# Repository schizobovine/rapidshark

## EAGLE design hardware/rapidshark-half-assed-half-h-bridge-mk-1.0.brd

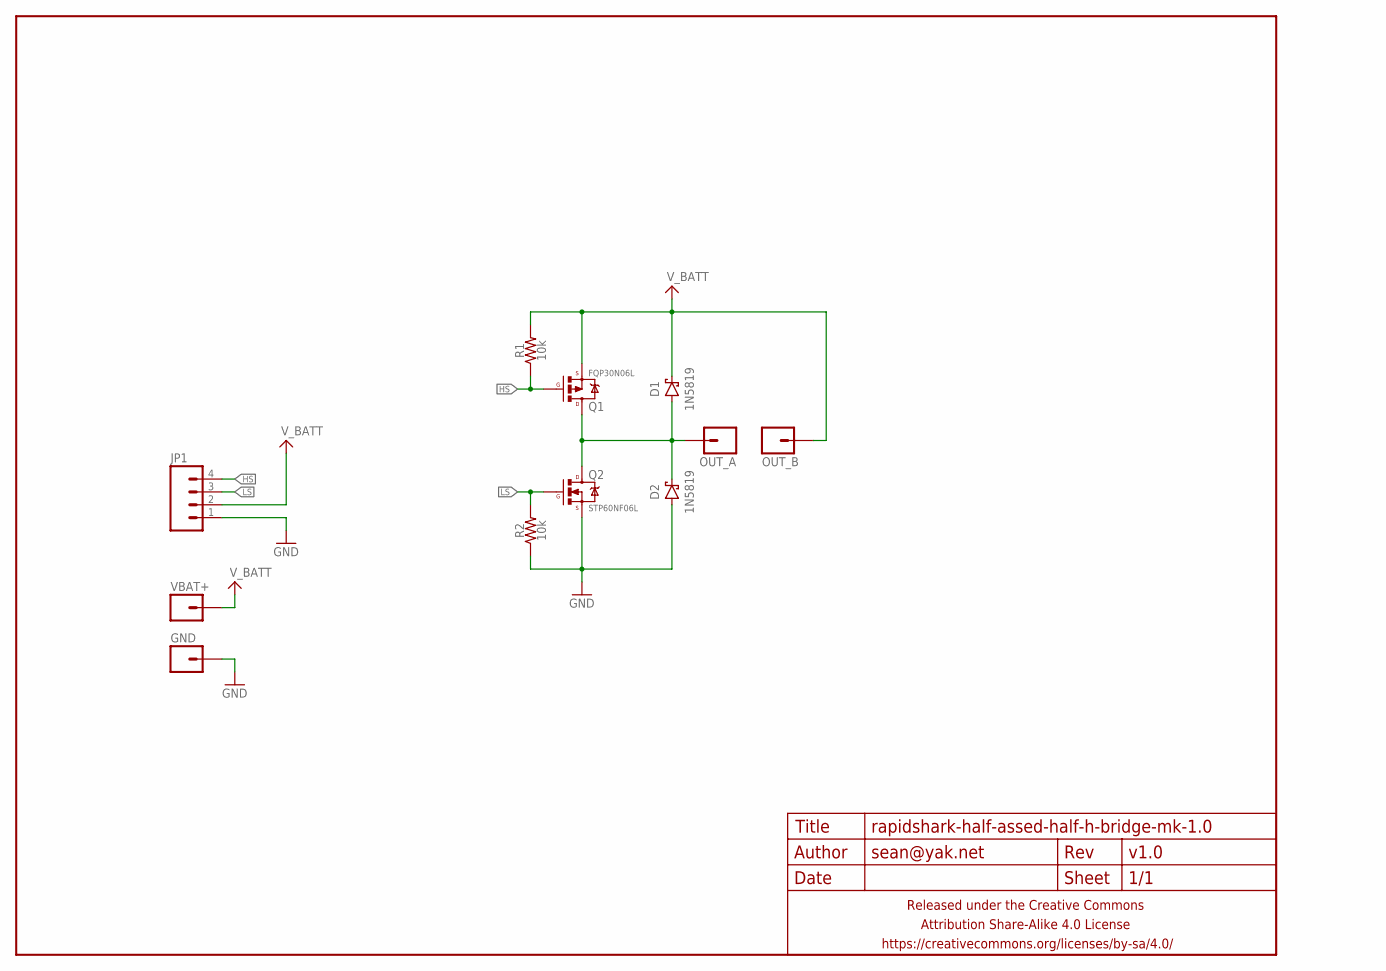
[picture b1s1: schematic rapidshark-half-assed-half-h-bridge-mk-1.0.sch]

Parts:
D1, D2: 1N5819; DIODE-SCHOTTKY-10.16MM
FRAME1: FRAME-LETTERNO_PACKAGE; DUMMY
GND: M0112AWG; 1X01-12AWG
JP1: M04PTH; 1X04-PTH-VERT
OUT_A: M0112AWG; 1X01-12AWG
OUT_B: M0112AWG; 1X01-12AWG
Q1: FQP30N06L; TO220-THERMPAD
Q2: STP60NF06L; TO220-THERMPAD
R1, R2: 10k; RESISTOR-AXIAL-PTH-5.08MM
VBAT+: M0112AWG; 1X01-12AWG

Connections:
A: D1.A, D2.C, OUT_A.1, Q1.2@1 (D), Q1.2@2 (D), Q2.2@1 (D), Q2.2@2 (D)
GND: D2.A, GND.1, JP1.1, Q2.3 (S), R2.P$1 (1)
HS: JP1.4, Q1.1 (G), R1.P$1 (1)
LS: JP1.3, Q2.1 (G), R2.P$2 (2)
V_BATT: D1.C, JP1.2, OUT_B.1, Q1.3 (S), R1.P$2 (2), VBAT+.1

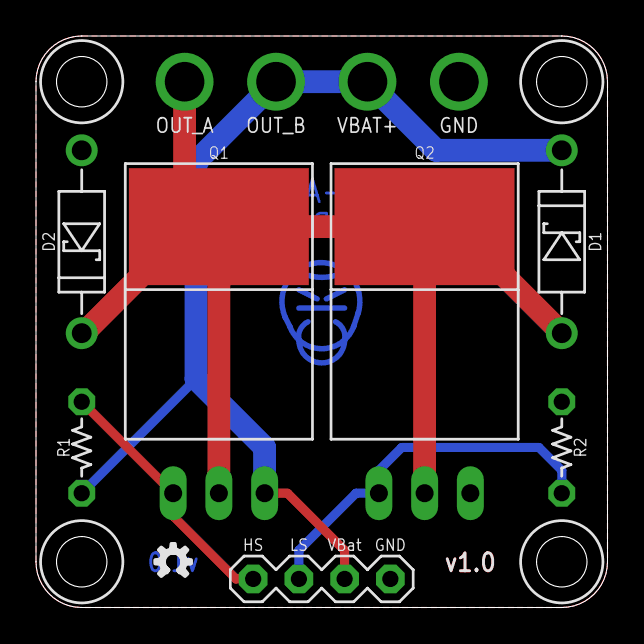
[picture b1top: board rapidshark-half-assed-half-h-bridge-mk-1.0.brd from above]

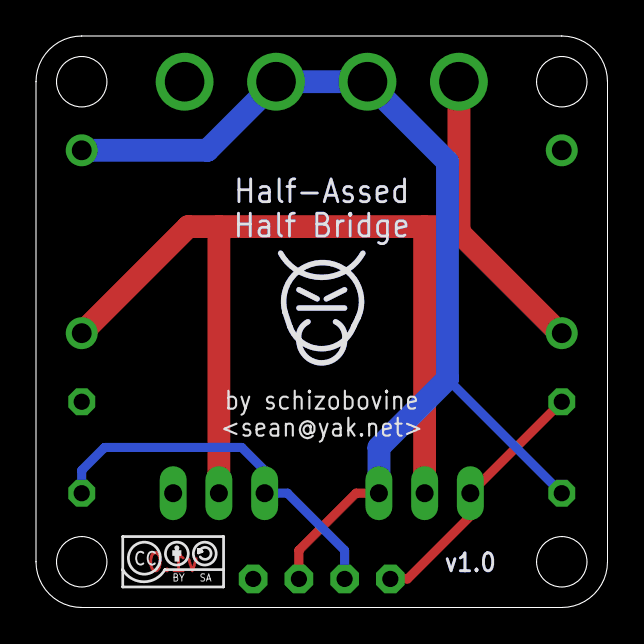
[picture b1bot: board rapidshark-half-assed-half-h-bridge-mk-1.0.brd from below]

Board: 2 copper layers, 31.8 x 31.8 mm, 15 parts (3 on the bottom side), 5 nets.

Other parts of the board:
U$1: COW_SMALL_METAL_NOTEXT
U$2: CC-BY-SA-4.0-NO-URL
U$3: OSHWLOGO_TINY_SILKONLY

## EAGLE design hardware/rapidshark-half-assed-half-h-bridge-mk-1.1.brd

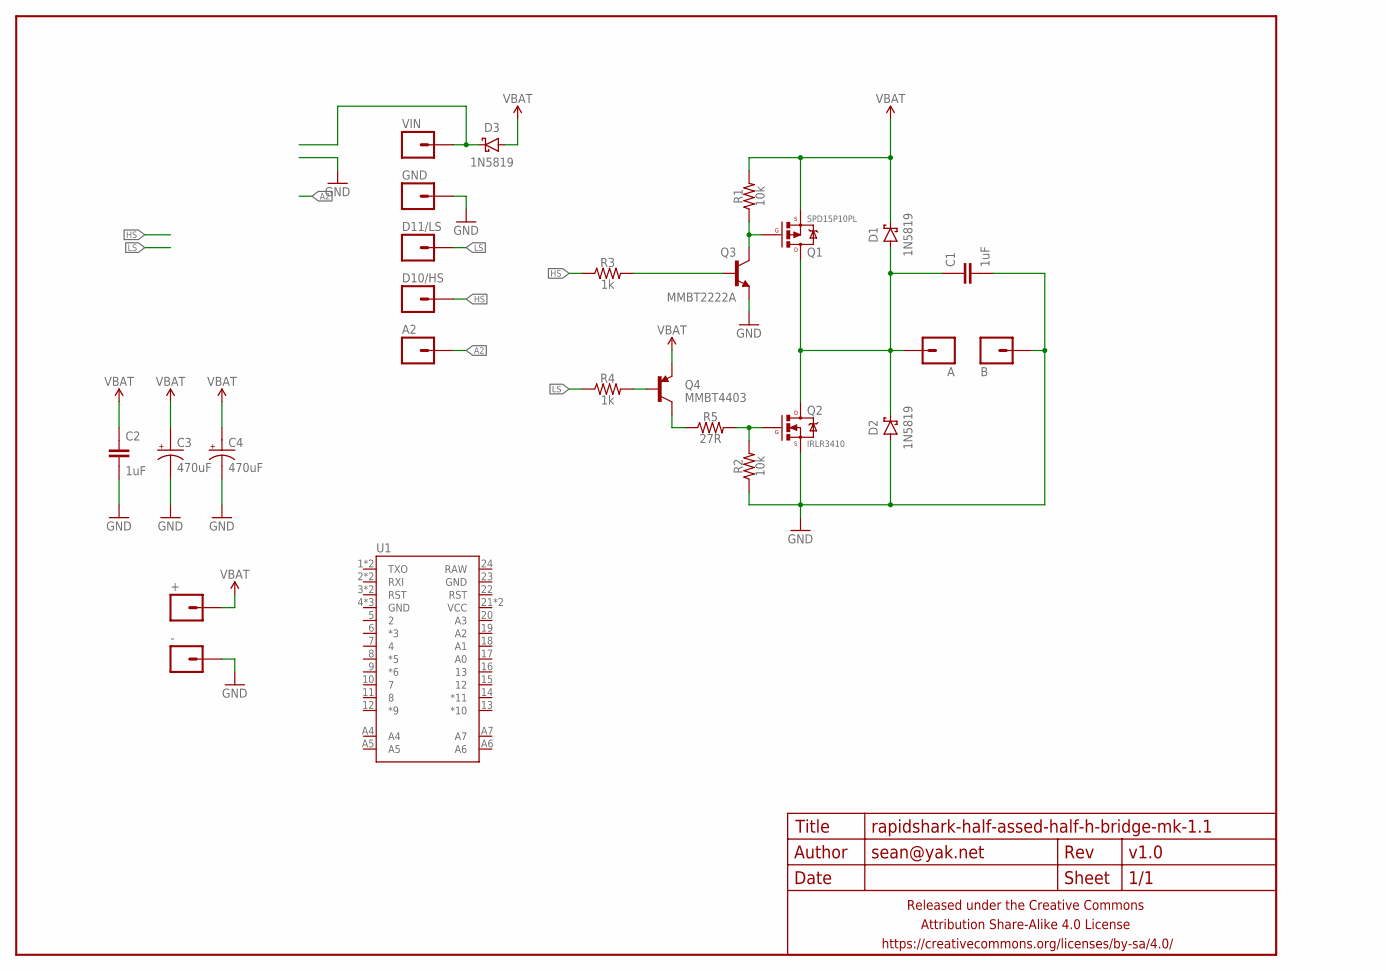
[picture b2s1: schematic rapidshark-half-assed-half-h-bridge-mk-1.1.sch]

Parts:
+: M01PTH-1.4MM; 1X01-1.4MM-CIR
-: M01PTH-1.4MM; 1X01-1.4MM-CIR
A: M01PTH-1.4MM; 1X01-1.4MM-CIR
A2: M01PTH; 1X01
B: M01PTH-1.4MM; 1X01-1.4MM-CIR
C1, C2: 1uF; C0603-TIGHTER
C3, C4: 470uF; E5-10,5
D1, D2: 1N5819; SMA-DIODE-SCHOTTKY
D3: 1N5819; SOD323-SCHOTTKY
D10/HS, D11/LS: M01PTH; 1X01
FRAME1: FRAME-LETTERNO_PACKAGE; DUMMY
GND: M01PTH; 1X01
Q1: SPD15P10PL; DPAK
Q2: IRLR3410; DPAK
Q3: MMBT2222A; SOT23
Q4: MMBT4403; SOT23
R1, R2: 10k; R0603-TIGHTER
R3, R4: 1k; R0603-TIGHTER
R5: 27R; R0603-TIGHTER
U1: ARDUINO_PRO_MINIMINE; ARDUINO_PRO_MINI_MINE
VIN: M01PTH; 1X01

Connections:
A: A.P$1, C1.1, D1.A, D2.C, Q1.4 (D), Q2.4 (D)
GND: -.P$1, B.P$1, C1.2, C2.2, C3.-, C4.-, D2.A, GND.1, Q2.3 (S), Q3.2 (E), R2.1
HS: D10/HS.1, R3.1
LS: D11/LS.1, R4.1
unnamed: Q1.1 (G), Q3.3 (C), R1.1
unnamed: Q2.1 (G), R2.2, R5.2
unnamed: Q3.1 (B), R3.2
unnamed: Q4.1 (B), R4.2
unnamed: Q4.3 (C), R5.1
unnamed: D3.C, VIN.1
VBAT: +.P$1, C2.1, C3.+, C4.+, D1.C, D3.A, Q1.3 (S), Q4.2 (E), R1.2

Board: 2 copper layers, 30 parts (23 on the bottom side), 11 nets, no tracks yet.

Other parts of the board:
U$1: COW_SMALL_METAL_NOTEXT
U$2: CC-BY-SA-4.0-NO-URL
U$3: OSHWLOGO_TINY_SILKONLY

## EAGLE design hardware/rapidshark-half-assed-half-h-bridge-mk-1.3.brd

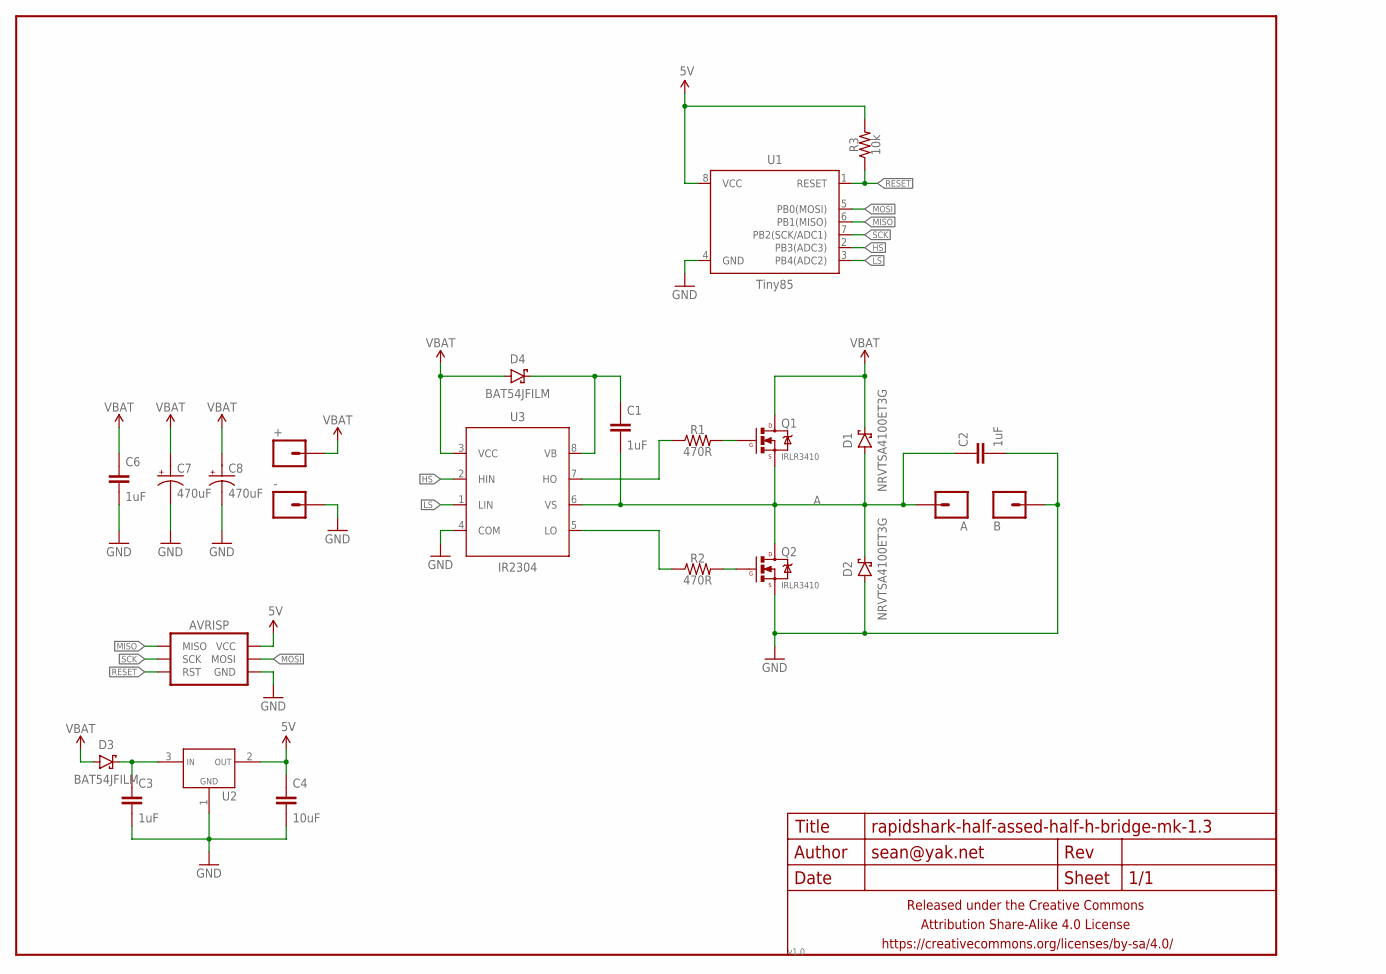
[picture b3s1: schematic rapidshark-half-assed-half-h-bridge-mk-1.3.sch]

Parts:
+: M01PTH-1.4MM; 1X01-1.4MM-CIR
-: M01PTH-1.4MM; 1X01-1.4MM-CIR
A: M01PTH-1.4MM; 1X01-1.4MM-CIR
AVRISP: AVR_SPI_PRG_6INLINE; AVR_MINI_PROG
B: M01PTH-1.4MM; 1X01-1.4MM-CIR
C1, C2, C3, C6: 1uF; C0603-TIGHTER
C4: 10uF; C0805-TIGHTER
C7, C8: 470uF; E5-10,5
D1, D2: NRVTSA4100ET3G; SMA-DIODE-SCHOTTKY
D3, D4: BAT54JFILM; SOD323-SCHOTTKY
FRAME1: FRAME-LETTERNO_PACKAGE; DUMMY
Q1, Q2: IRLR3410; DPAK
R1, R2: 470R; R0603-TIGHTER
R3: 10k; R0603-TIGHTER
U1: Tiny85; SO08-EIAJ
U2: VREG_1117SOT-23; SOT23
U3: IR2304; SO08

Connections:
5V: AVRISP.2 (VCC), C4.1, R3.2, U1.8 (VCC), U2.2 (VOUT)
A: A.P$1, C1.2, C2.1, D1.A, D2.C, Q1.3 (S), Q2.4 (D), U3.6 (VS)
GND: -.P$1, AVRISP.6 (GND), B.P$1, C2.2, C3.2, C4.2, C6.2, C7.-, C8.-, D2.A, Q2.3 (S), U1.4 (GND), U2.1 (GND), U3.4 (COM)
HS: U1.2 (PB3(ADC3)), U3.2 (HIN)
LS: U1.3 (PB4(ADC2)), U3.1 (LIN)
MISO: AVRISP.1 (MISO), U1.6 (PB1(MISO))
MOSI: AVRISP.4 (MOSI), U1.5 (PB0(MOSI))
unnamed: Q1.1 (G), R1.2
unnamed: Q2.1 (G), R2.2
unnamed: R1.1, U3.7 (HO)
unnamed: R2.1, U3.5 (LO)
unnamed: C1.1, D4.C, U3.8 (VB)
unnamed: C3.1, D3.C, U2.3 (VIN)
RESET: AVRISP.5 (RST), R3.1, U1.1 (RESET)
SCK: AVRISP.3 (SCK), U1.7 (PB2(SCK/ADC1))
VBAT: +.P$1, C6.1, C7.+, C8.+, D1.C, D3.A, D4.A, Q1.4 (D), U3.3 (VCC)

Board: 2 copper layers, 28 parts (4 on the bottom side), 16 nets, no tracks yet.

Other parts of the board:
U$1: COW_SMALL_METAL_NOTEXT
U$2: CC-BY-SA-4.0-NO-URL
U$3: OSHWLOGO_TINY_SILKONLY

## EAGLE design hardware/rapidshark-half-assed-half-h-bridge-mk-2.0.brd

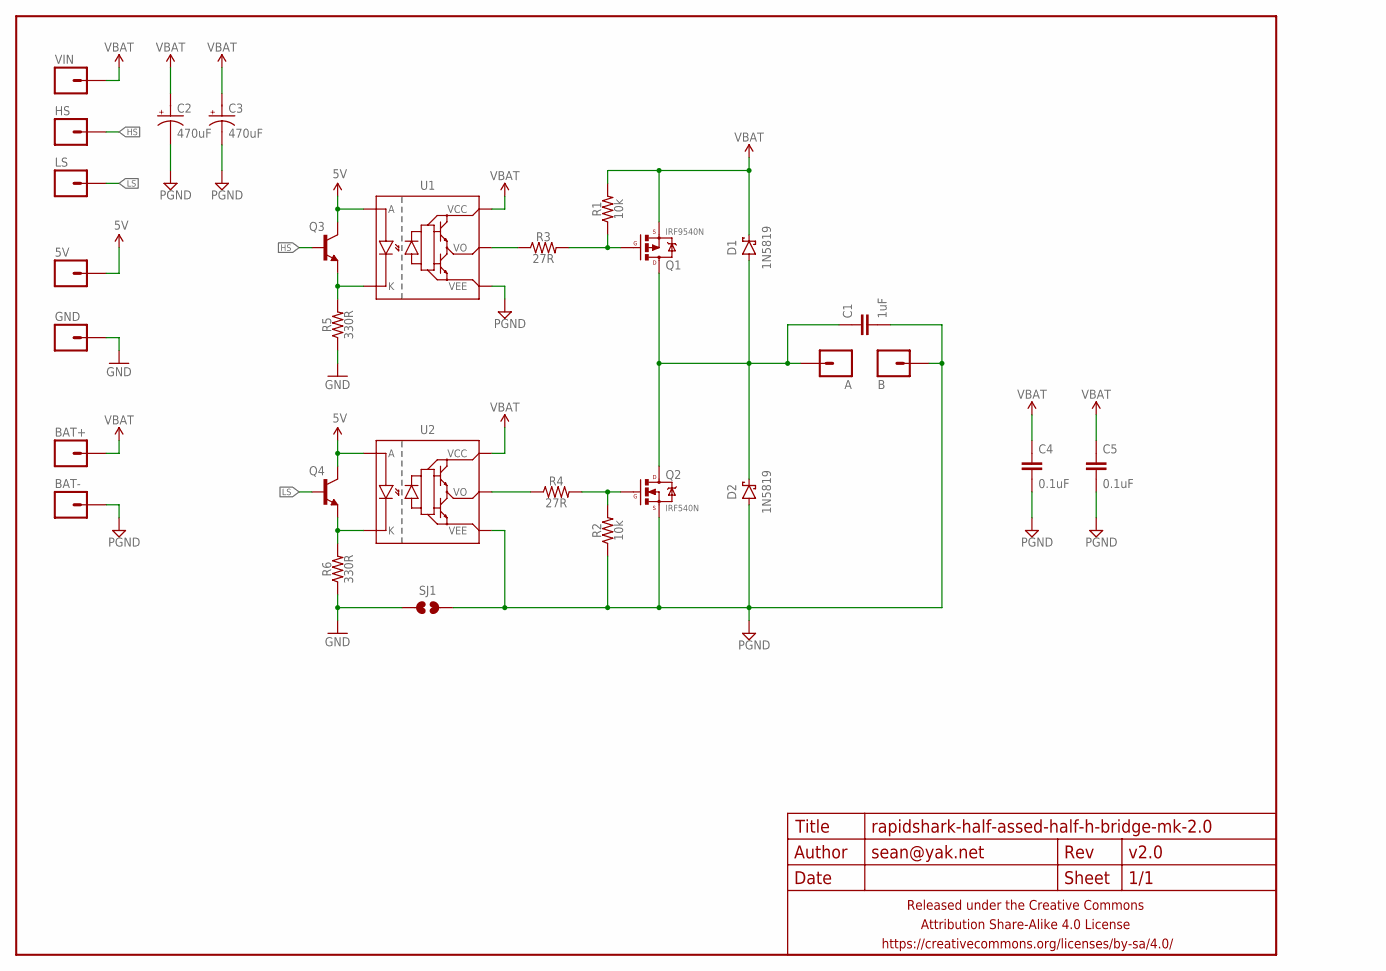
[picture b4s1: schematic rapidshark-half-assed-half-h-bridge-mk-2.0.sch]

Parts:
5V: M01PTH; 1X01
A: M01PTH-1.9MM; 1X01-1.9MM-CIR
B: M01PTH-1.9MM; 1X01-1.9MM-CIR
BAT+: M01PTH-1.9MM; 1X01-1.9MM-CIR
BAT-: M01PTH-1.9MM; 1X01-1.9MM-CIR
C1: 1uF; C0603-TIGHTER
C2, C3: 470uF; E5-10,5
C4, C5: 0.1uF; C0603-TIGHTER
D1, D2: 1N5819; SMA-DIODE-SCHOTTKY
FRAME1: FRAME-LETTERNO_PACKAGE; DUMMY
GND: M01PTH; 1X01
HS: M01PTH; 1X01
LS: M01PTH; 1X01
Q1: IRF9540N; D2PAK
Q2: IRF540N; D2PAK
Q3, Q4: TRANSISTOR_NPNMMBT2222A; SOT23
R1, R2: 10k; R0603-TIGHTER
R3, R4: 27R; R0603-TIGHTER
R5, R6: 330R; R0603-TIGHTER
SJ1: JUMPER-PAD-2-NO; PAD-JUMPER-2-NO_NO_SILK
U1, U2: OPTOISOLATOR-GATEDRIVERSOIC05; SO05
VIN: M01PTH; 1X01

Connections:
5V: 5V.1, Q3.3 (C), Q4.3 (C), U1.1 (A), U2.1 (A)
A: A.P$1, C1.1, D1.A, D2.C, Q1.D, Q2.D
GND: GND.1, R5.1, R6.1, SJ1.1
HS: HS.1, Q3.1 (B)
LS: LS.1, Q4.1 (B)
unnamed: Q2.G, R2.2, R4.2
unnamed: R3.1, U1.5 (VO)
unnamed: Q3.2 (E), R5.2, U1.3 (K)
unnamed: Q1.G, R1.1, R3.2
unnamed: Q4.2 (E), R6.2, U2.3 (K)
unnamed: R4.1, U2.5 (VO)
PGND: B.P$1, BAT-.P$1, C1.2, C2.-, C3.-, C4.2, C5.2, D2.A, Q2.S, R2.1, SJ1.2, U1.4 (VEE), U2.4 (VEE)
VBAT: BAT+.P$1, C2.+, C3.+, C4.1, C5.1, D1.C, Q1.S, R1.2, U1.6 (VCC), U2.6 (VCC), VIN.1

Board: 2 copper layers, 30 parts (2 on the bottom side), 13 nets, no tracks yet.

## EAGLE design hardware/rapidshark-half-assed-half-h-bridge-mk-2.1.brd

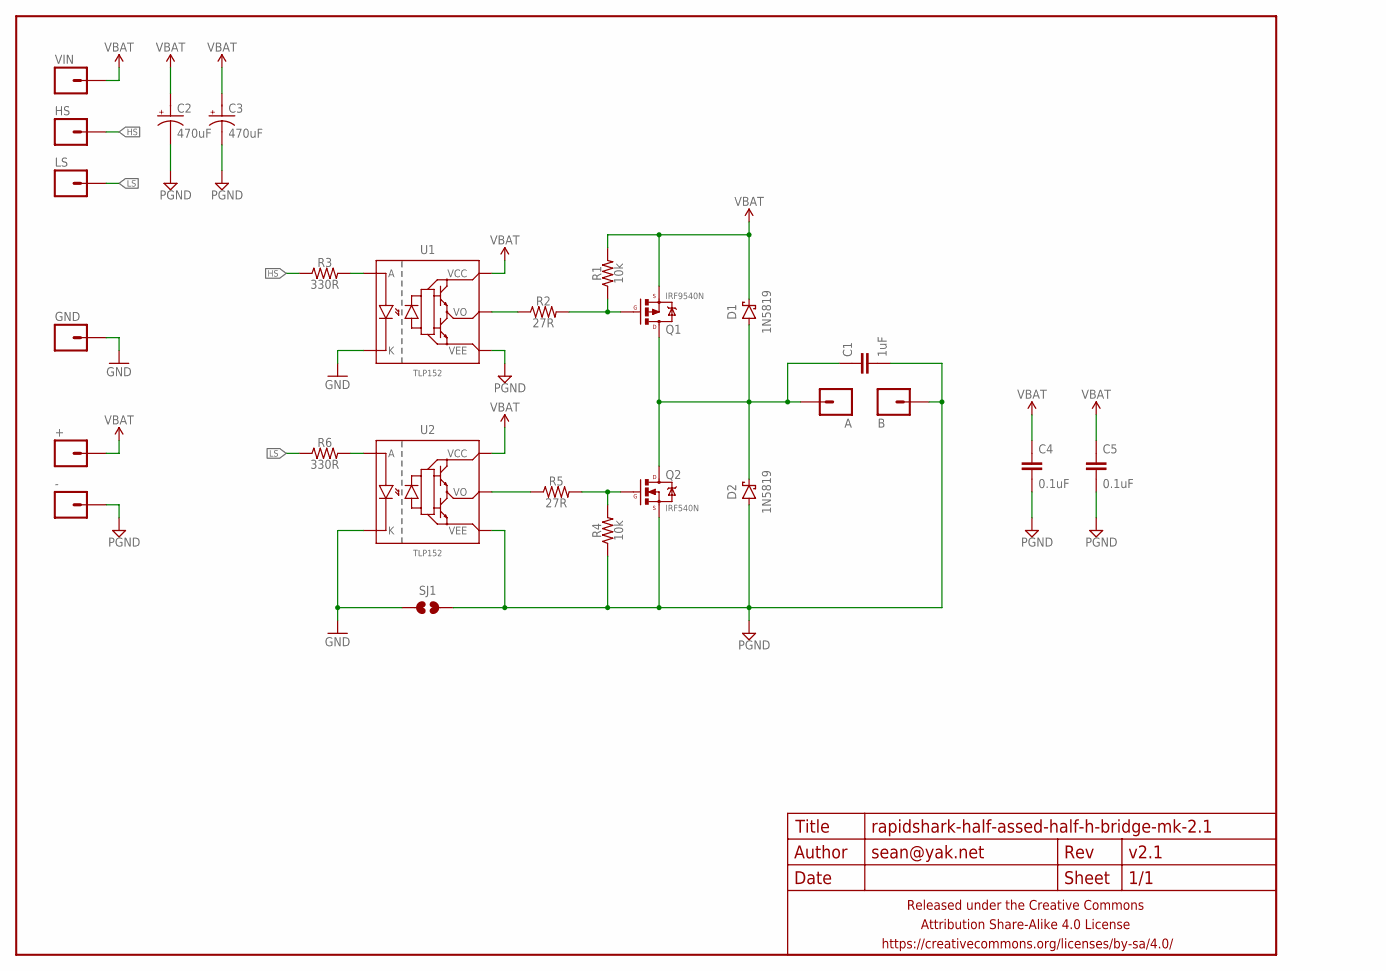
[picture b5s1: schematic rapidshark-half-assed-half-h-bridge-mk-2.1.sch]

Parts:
+: M01PTH-1.9MM; 1X01-1.9MM-CIR
-: M01PTH-1.9MM; 1X01-1.9MM-CIR
A: M01PTH-1.9MM; 1X01-1.9MM-CIR
B: M01PTH-1.9MM; 1X01-1.9MM-CIR
C1: 1uF; C0603-TIGHTER
C2, C3: 470uF; E5-10,5
C4, C5: 0.1uF; C0603-TIGHTER
D1, D2: 1N5819; SMA-DIODE-SCHOTTKY
FRAME1: FRAME-LETTERNO_PACKAGE; DUMMY
GND: M01PTH; 1X01
HS: M01PTH; 1X01
LS: M01PTH; 1X01
Q1: IRF9540N; D2PAK
Q2: IRF540N; D2PAK
R1, R4: 10k; R0603-TIGHTER
R2, R5: 27R; R0603-TIGHTER
R3, R6: 330R; R0603-TIGHTER
SJ1: JUMPER-PAD-2-NO; PAD-JUMPER-2-NO_NO_SILK
U1, U2: TLP152; SO05
VIN: M01PTH; 1X01

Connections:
A: A.P$1, C1.1, D1.A, D2.C, Q1.D, Q2.D
GND: GND.1, SJ1.1, U1.3 (K), U2.3 (K)
HS: HS.1, R3.1
LS: LS.1, R6.1
unnamed: Q2.G, R4.2, R5.2
unnamed: R2.1, U1.5 (VO)
unnamed: R6.2, U2.1 (A)
unnamed: R3.2, U1.1 (A)
unnamed: Q1.G, R1.1, R2.2
unnamed: R5.1, U2.5 (VO)
PGND: -.P$1, B.P$1, C1.2, C2.-, C3.-, C4.2, C5.2, D2.A, Q2.S, R4.1, SJ1.2, U1.4 (VEE), U2.4 (VEE)
VBAT: +.P$1, C2.+, C3.+, C4.1, C5.1, D1.C, Q1.S, R1.2, U1.6 (VCC), U2.6 (VCC), VIN.1

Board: 2 copper layers, 27 parts (2 on the bottom side), 12 nets, no tracks yet.

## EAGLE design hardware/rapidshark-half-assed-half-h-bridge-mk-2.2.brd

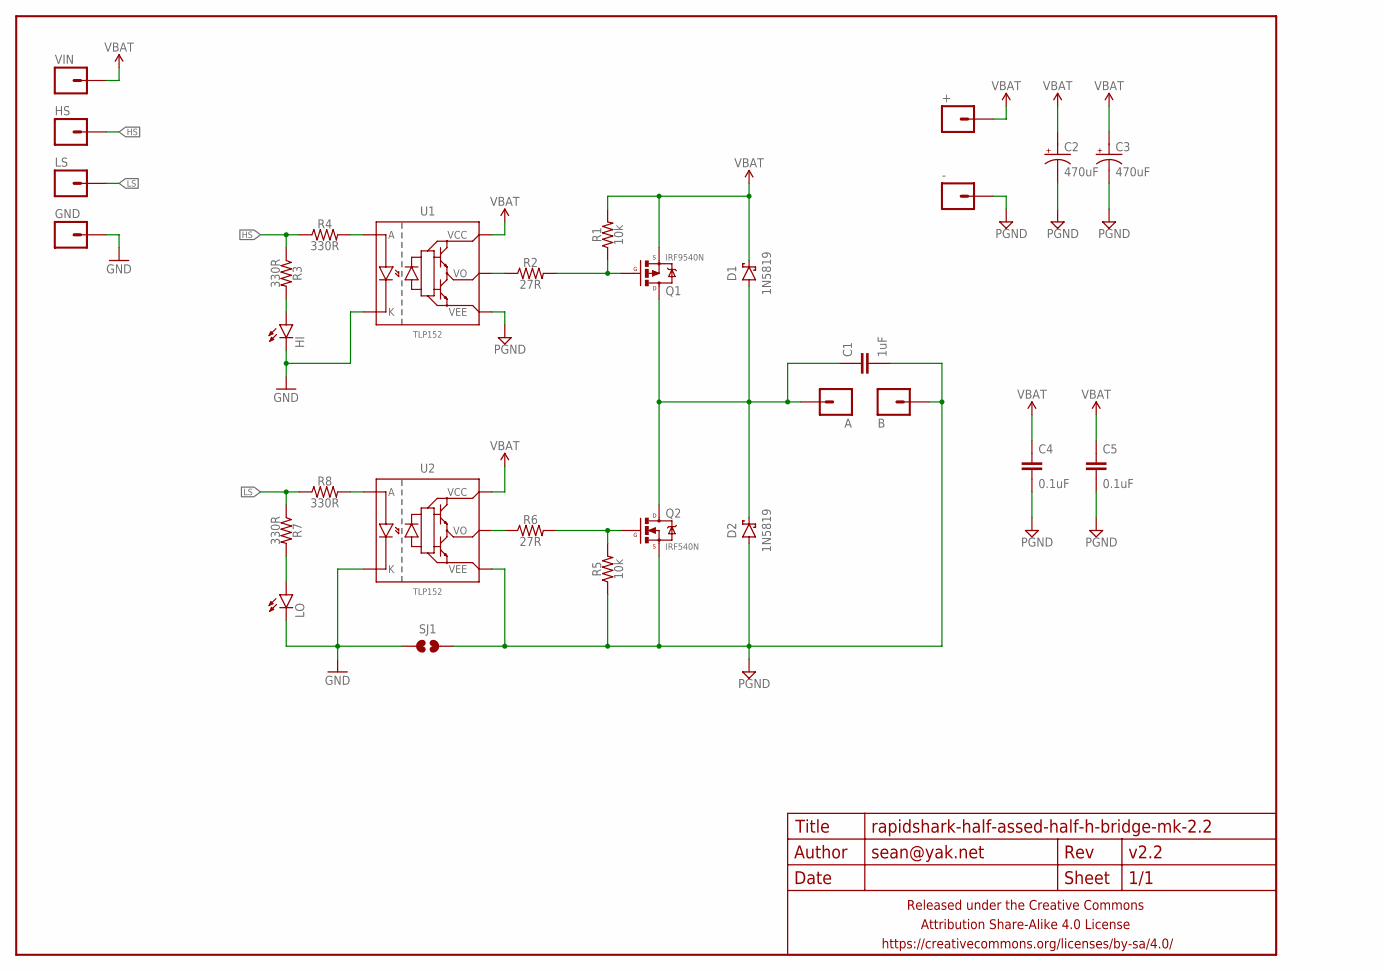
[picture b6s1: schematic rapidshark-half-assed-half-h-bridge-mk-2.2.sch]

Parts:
+: M01PTH-1.9MM; 1X01-1.9MM-CIR
-: M01PTH-1.9MM; 1X01-1.9MM-CIR
A: M01PTH-1.9MM; 1X01-1.9MM-CIR
B: M01PTH-1.9MM; 1X01-1.9MM-CIR
C1: 1uF; C0603-TIGHTER
C2, C3: 470uF; E5-10,5
C4, C5: 0.1uF; C0603-TIGHTER
D1, D2: 1N5819; SMA-DIODE-SCHOTTKY
FRAME1: FRAME-LETTERNO_PACKAGE; DUMMY
GND: M01PTH; 1X01
HI: LED0603-TIGHT; LED-0603-TIGHT
HS: M01PTH; 1X01
LO: LED0603-TIGHT; LED-0603-TIGHT
LS: M01PTH; 1X01
Q1: IRF9540N; D2PAK
Q2: IRF540N; D2PAK
R1, R5: 10k; R0603-TIGHTER
R2, R6: 27R; R0603-TIGHTER
R3, R4, R7, R8: 330R; R0603-TIGHTER
SJ1: JUMPER-PAD-2-NO; PAD-JUMPER-2-NO_NO_SILK
U1, U2: TLP152; SO05
VIN: M01PTH; 1X01

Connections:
A: A.P$1, C1.1, D1.A, D2.C, Q1.D, Q2.D
GND: GND.1, HI.C, LO.C, SJ1.1, U1.3 (K), U2.3 (K)
HS: HS.1, R3.1, R4.1
LS: LS.1, R7.1, R8.1
unnamed: Q2.G, R5.2, R6.2
unnamed: R2.1, U1.5 (VO)
unnamed: LO.A, R7.2
unnamed: HI.A, R3.2
unnamed: Q1.G, R1.1, R2.2
unnamed: R4.2, U1.1 (A)
unnamed: R8.2, U2.1 (A)
unnamed: R6.1, U2.5 (VO)
PGND: -.P$1, B.P$1, C1.2, C2.-, C3.-, C4.2, C5.2, D2.A, Q2.S, R5.1, SJ1.2, U1.4 (VEE), U2.4 (VEE)
VBAT: +.P$1, C2.+, C3.+, C4.1, C5.1, D1.C, Q1.S, R1.2, U1.6 (VCC), U2.6 (VCC), VIN.1

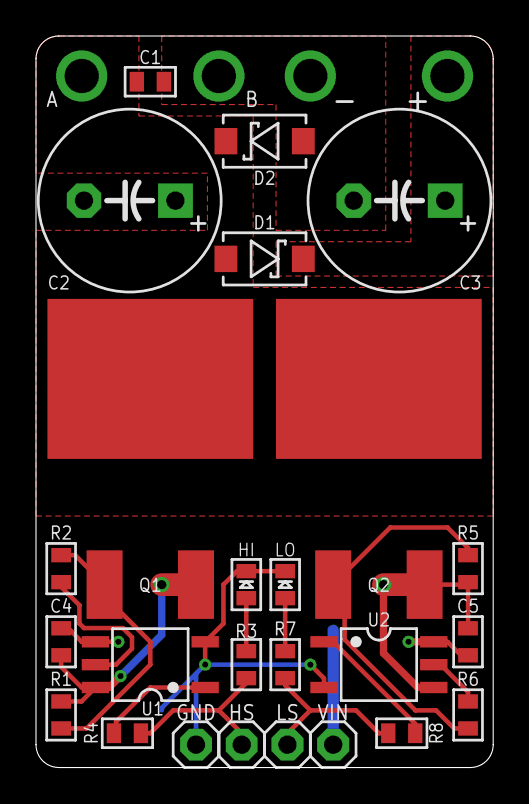
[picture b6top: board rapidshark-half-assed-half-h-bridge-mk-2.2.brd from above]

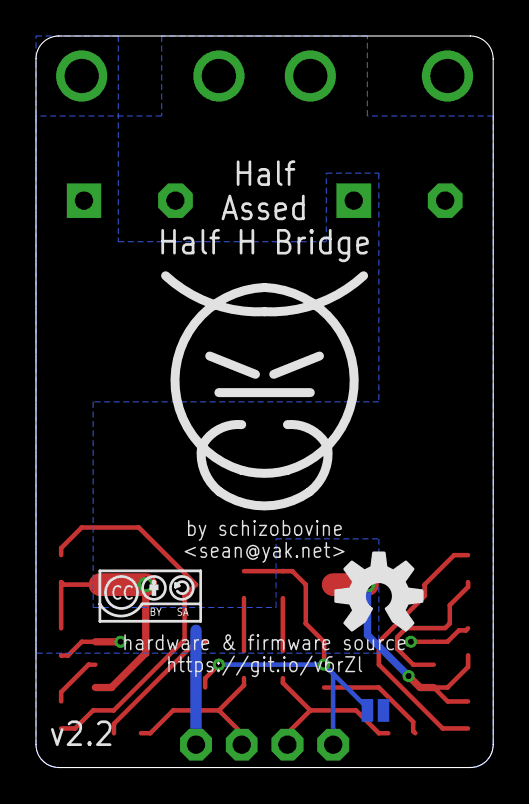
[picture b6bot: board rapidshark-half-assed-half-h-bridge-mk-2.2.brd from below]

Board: 2 copper layers, 25.4 x 40.6 mm, 34 parts (5 on the bottom side), 14 nets.

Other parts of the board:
U$1: COW
U$2: CC-BY-SA-4.0-NO-URL
U$3: OSHWLOGO_5MM

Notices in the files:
parts and their libraries:
A_butts: Released under the Creative Commons Attribution Share-Alike 4.0 License
A_butts: https://creativecommons.org/licenses/by-sa/4.0
A_butts: Released under the Creative Commons
